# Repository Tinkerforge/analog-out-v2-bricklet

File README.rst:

Analog Out Bricklet 2.0
=======================

This repository contains the firmware source code and the hardware design
files. The documentation generator configs can be found at
https://github.com/Tinkerforge/generators

Repository Content
------------------

software/:
 * examples/: Examples for all supported languages
 * build/: Compiled files
 * src/: Source code of firmware
 * Makefile: Makefile to build project

hardware/:
 * Contains KiCad project files and additionally schematics as PDF

datasheets/:
 * Contains datasheets for sensors and complex ICs that are used

Hardware
--------

The hardware is designed with the open source EDA Suite KiCad
(http://www.kicad.org). Before you are able to open the files,
you have to install the Tinkerforge kicad-libraries
(https://github.com/Tinkerforge/kicad-libraries). You can either clone
them directly in hardware/ or clone them in a separate folder and
symlink them into hardware/
(ln -s kicad_path/kicad-libraries project_path/hardware). After that you
can open the .pro file in hardware/ with KiCad and from there view and
modify the schematics and the PCB layout.

Software
--------

If you want to do your own Brick/Bricklet firmware development we highly
recommend that you use our build environment setup script and read the
tutorial (https://www.tinkerforge.com/en/doc/Tutorials/Tutorial_Build_Environment/Tutorial.html).

To compile the C code we recommend you to install the newest GNU Arm Embedded
Toolchain (https://launchpad.net/gcc-arm-embedded/+download).
You also need to install bricklib (https://github.com/Tinkerforge/bricklib)
and brickletlib (https://github.com/Tinkerforge/brickletlib).

You can either clone it directly in software/src/ or clone it in a
separate folder and symlink it into software/src/
(ln -s bricklib_path/bricklib project_path/software/src/ and
ln -s brickletlib_path/brickletlib project_path/software/src/).
Finally make sure to have CMake installed
(http://www.cmake.org/cmake/resources/software.html).

After that you can build the firmware by invoking make in software/.
The firmware (.bin) can then be found in software/build/ and uploaded
with brickv (click button "Flashing" on start screen).

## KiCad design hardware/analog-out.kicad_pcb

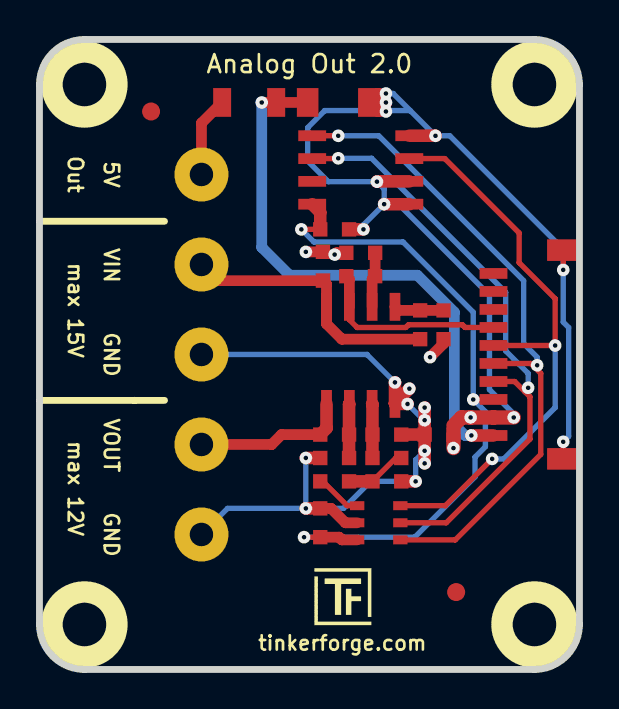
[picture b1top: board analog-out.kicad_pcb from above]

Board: 2 copper layers, 30.0 x 35.0 mm, 30 parts (0 on the bottom side), 17 nets.

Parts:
C1, C2, C3: 100nF; C0603
C4: 180pF; C0603
D1: 5V; MiniMelf
F1: OZCJ0035FF2G; F1206
Fiducial_Mark: VAL**; Fiducial_Mark
Fiducial_Mark#2: VAL**; Fiducial_Mark
P1: CON-SENSOR
P2: CONN_5; AKL_5_5
R1: 68.1; R0603
R2: 0; R0603
R3, R4: 3k3; R0603
R5, R6, R7, R8: 12k; R0603
R9, R10: 68k; R0603
Ref**: Val**; Logo_31x31
U1: M24C64; SOIC8
U2: MCP4725A0; SOT23-6
U3: TLV272IS; SOIC8
U4, U5, U6, U7: DRILL; DRILL_NP
VAL: CE_5mm
VAL#2: WEEE_7mm

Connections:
3V3: C2.1, C3.1, P1.3, U1.8, U2.3
+5V: D1.2, F1.1, P1.1
AGND: C1.2, C2.2, C4.2, P2.1, P2.3, R2.2, R3.2, R6.2, R7.2, R9.1, U2.2, U3.4
GND: C3.2, D1.1, P1.2, P1.EP, R2.1, U1.1, U1.2, U1.4
unnamed: C4.1, R1.1, R4.1
unnamed: F1.2, P2.5
unnamed: P1.6, U1.3, U2.6
unnamed: P1.7, R5.2, U3.7
unnamed: P2.2, R8.1, U3.1
unnamed: R1.2, U2.1
unnamed: R3.1, R8.2, U3.2
unnamed: R4.2, R6.1, U3.3
unnamed: R5.1, R9.2, U3.6
unnamed: R7.1, R10.2, U3.5
SCL: P1.4, U1.6, U2.5
SDA: P1.5, U1.5, U2.4
VCC: C1.1, P2.4, R10.1, U3.8

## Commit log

2015-03-03 Add first adaption from V1 to V2
    Missing:
    - Correct voltage input calculation (currently still for V1)
    - API to get and force specified voltage for input
2015-03-27 checkin of hardware files of V2 version
2015-03-30 change output voltage to max 12V
2015-03-31 Implement API for Analog In V2
2015-03-31 Add datasheet of MCP4725
2015-03-31 add second ground connector add fuse and z-diode for 5V rail
2015-03-31 missing changes from last commit
2015-04-02 order version
2015-04-02 change port description
2015-04-16 Fix display name in readme
2015-04-16 Add .gitignore
2015-04-16 specify fuse
2015-04-23 Add Python example
2015-04-24 change voltage devider to opamp differential amplifier
2015-04-24 drc executed
2015-05-04 Calculate voltage as used in production version
2015-05-05 Add C/C++ example
2015-05-05 Add C# example
2015-05-05 Add Delphi examples
2015-05-05 Add Java example
2015-05-05 Add JavaScript examples
2015-05-05 Add Perl examples
2015-05-05 Add PHP example
2015-05-05 Add Ruby example
2015-05-05 Add Shell example
2015-05-05 Add VB.NET example
2015-05-05 Add matlab/octave examples
2015-05-05 Add Mathematica examples
2015-05-05 Remove faulty .txt
2015-06-18 Add LabVIEW and update Mathematica examples
    Also clean up other examples.
2015-07-23 Make JavaScript browser example textarea readonly
2015-07-27 adapt schematic acording to symbol change, add PDF schematic
2015-07-27 Cleanup C/C++ and Java examples
2015-07-29 Reformat changelog
2015-08-07 Use full device class name in Python examples
2015-08-12 Fix minor warnings in C/C++ example
2015-08-14 Cleanup Delphi example
2015-08-19 Whitespace
2015-09-09 Duplicate cmake call to fix bug during cmake creation
2015-09-17 Generator based example cleanup
2015-11-12 matlab: Fix callback handling for R2014a
    http://undocumentedmatlab.com/blog/matlab-callbacks-for-java-events-in-r2014a
2015-11-25 Include date and commit into changelog
2016-05-18 c: Add missing device destroy call
2016-07-01 Make the change UID comment more explicit
2017-06-02 octave: Use javaObject instead of deprecated java_new
2017-08-01 use tinkerforge symbols instead of kicad symbols
2017-08-01 Add 3d information (final)
2017-08-01 Add 3d model (*.step & *.FCStd)
2017-08-03 Rename *.FCStd file
2017-12-07 mathematica: Also generate .nb files
2018-02-19 javascript: Close div tag correctly
2018-02-20 Cleanup KiCad libraries config
    Ensure LibDir=kicad-libraries and LibName1=tinkerforge.
    Remove special library.
2018-05-11 Rename files
2018-05-24 perl: Use strict in examples
2018-07-11 Add Makefile with docker support
2018-07-11 Update directory structure and build instructions
2018-07-11 Remove obsolete generate_makefile scripts
2018-11-07 rust: Accept host names for ip connection, fix naming inconsistencies
2018-12-14 Add go examples.
2018-12-18 go: Change import path.
2018-12-18 go: Change import path again.
2018-12-20 rust: Reformat examples.
2019-01-24 mqtt: Add examples.
2019-01-24 mqtt: Fix example header.
2019-01-24 mqtt: Remove executable bit in example permissions.
2019-01-24 go: Minor example fixes.
2020-01-13 examples: Use python3 input instead of python2 raw_input.
2020-04-07 examples: rust: Always block when calling bindings functions.
2021-10-25 Update KiCad link
    https://www.kicad.org/blog/2021/10/Avoid-links-to-former-kicad-domain/
2022-07-06 Add license files.

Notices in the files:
hardware/analog-out.kicad_pcb:
Licensed under CERN OHL v.1.1
Copyright (©) 2015, B.Nordmeyer
Copyright Tinkerforge GmbH 2015.
This documentation describes Open Hardware and is licensed under the
CERN OHL v. 1.1.
